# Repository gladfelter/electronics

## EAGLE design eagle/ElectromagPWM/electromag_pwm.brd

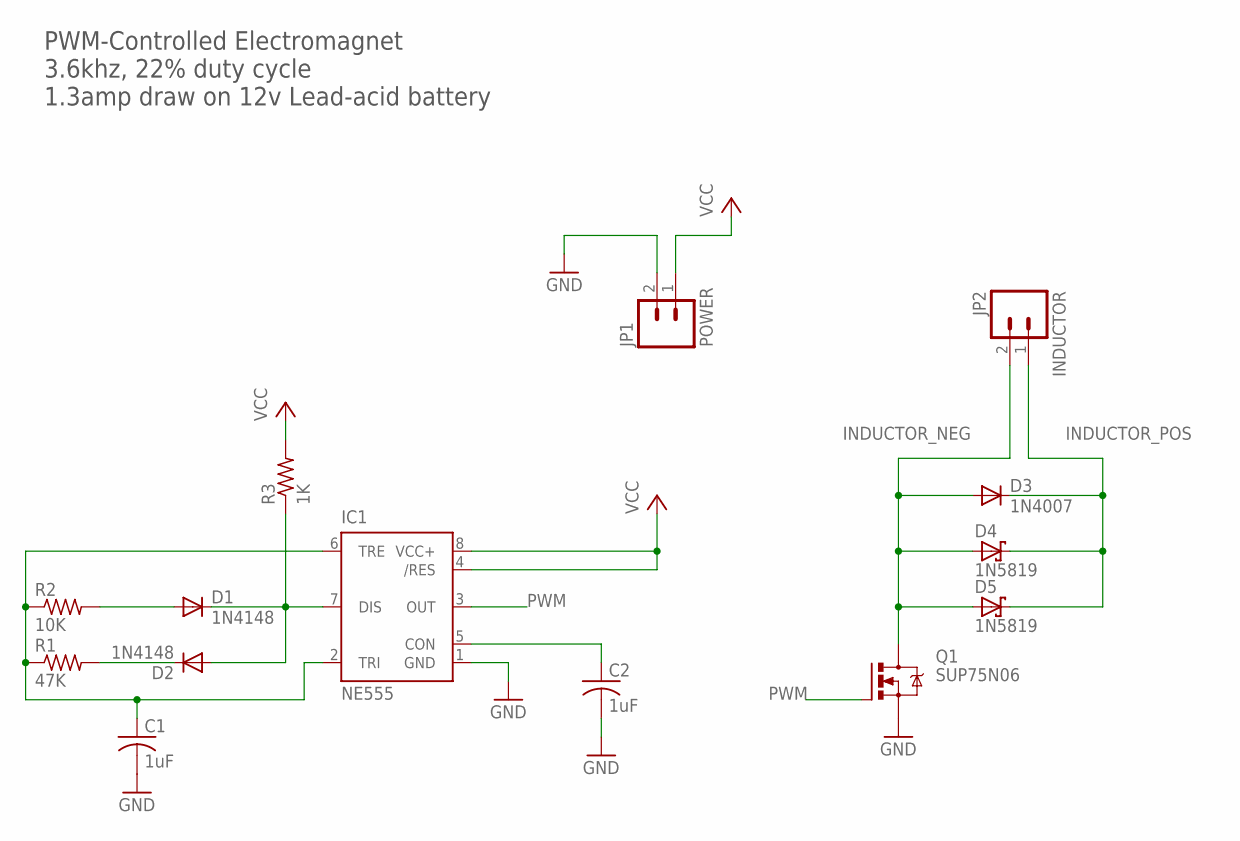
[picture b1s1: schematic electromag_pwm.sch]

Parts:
C1, C2: 1uF; C025-025X050
D1, D2: 1N4148; DO35-7
D3: 1N4007; DO41-10
D4, D5: 1N5819; DO41-7.6
IC1: NE555; DIL-08
JP1: POWER; JST-2-PTH-VERT
JP2: INDUCTOR; JST-2-PTH-VERT
Q1: SUP75N06; TO220BH
R1: 47K; 0204/5
R2: 10K; 0204/5
R3: 1K; 0204/5

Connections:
GND: C1.2, C2.2, IC1.1 (GND), JP1.2, Q1.S
INDUCTOR_NEG: D3.A, D4.A, D5.A, JP2.2, Q1.D
INDUCTOR_POS: D3.C, D4.C, D5.C, JP2.1
unnamed: D2.C, R1.2
unnamed: D1.A, R2.2
unnamed: C2.1, IC1.5 (CON)
unnamed: C1.1, IC1.2 (TRI), IC1.6 (TRE), R1.1, R2.1
unnamed: D1.C, D2.A, IC1.7 (DIS), R3.1
PWM: IC1.3 (OUT), Q1.G
VCC: IC1.4 (/RES), IC1.8 (VCC+), JP1.1, R3.2

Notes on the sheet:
PWM-Controlled Electromagnet 3.6khz, 22% duty cycle 1.3amp draw on 12v Lead-acid battery

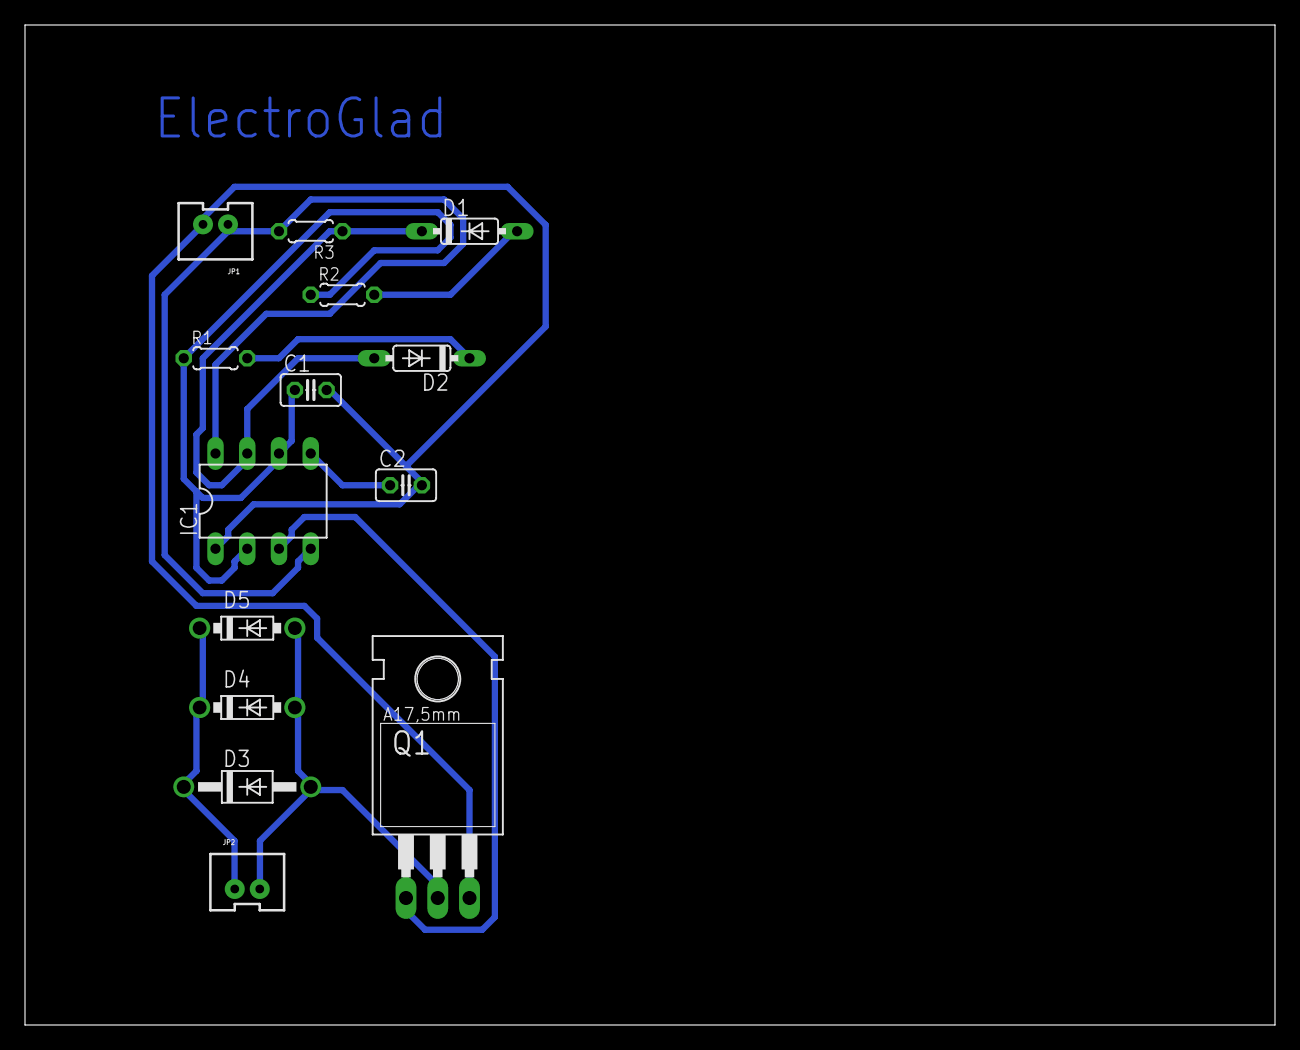
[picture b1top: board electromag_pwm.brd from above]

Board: 2 copper layers, 100.0 x 80.0 mm, 14 parts (0 on the bottom side), 10 nets.

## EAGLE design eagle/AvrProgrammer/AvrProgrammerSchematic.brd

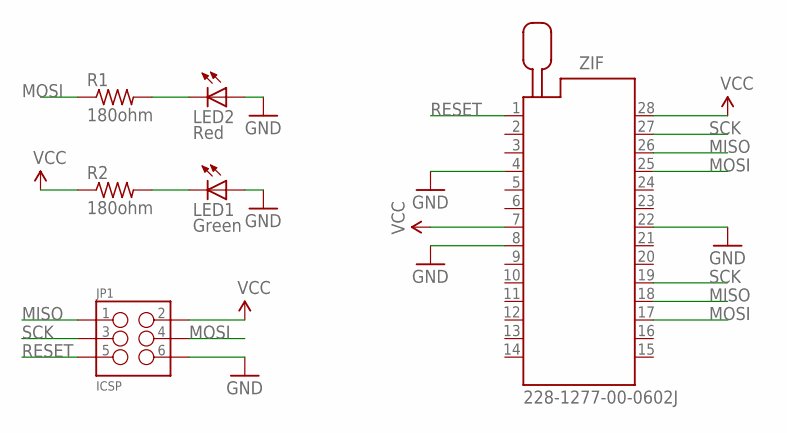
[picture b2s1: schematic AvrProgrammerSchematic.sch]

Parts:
JP1: ICSP; 2X3_SMD
LED1: Green; LED3MM
LED2: Red; LED3MM
R1, R2: 180ohm; 0207/7
ZIF: 228-1277-00-0602J

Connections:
GND: JP1.6, LED1.A, LED2.A, ZIF.4, ZIF.8, ZIF.22
MISO: JP1.1, ZIF.18, ZIF.26
MOSI: JP1.4, R1.1, ZIF.17, ZIF.25
unnamed: LED2.K (C), R1.2
unnamed: LED1.K (C), R2.2
RESET: JP1.5, ZIF.1
SCK: JP1.3, ZIF.19, ZIF.27
VCC: JP1.2, R2.1, ZIF.7, ZIF.28

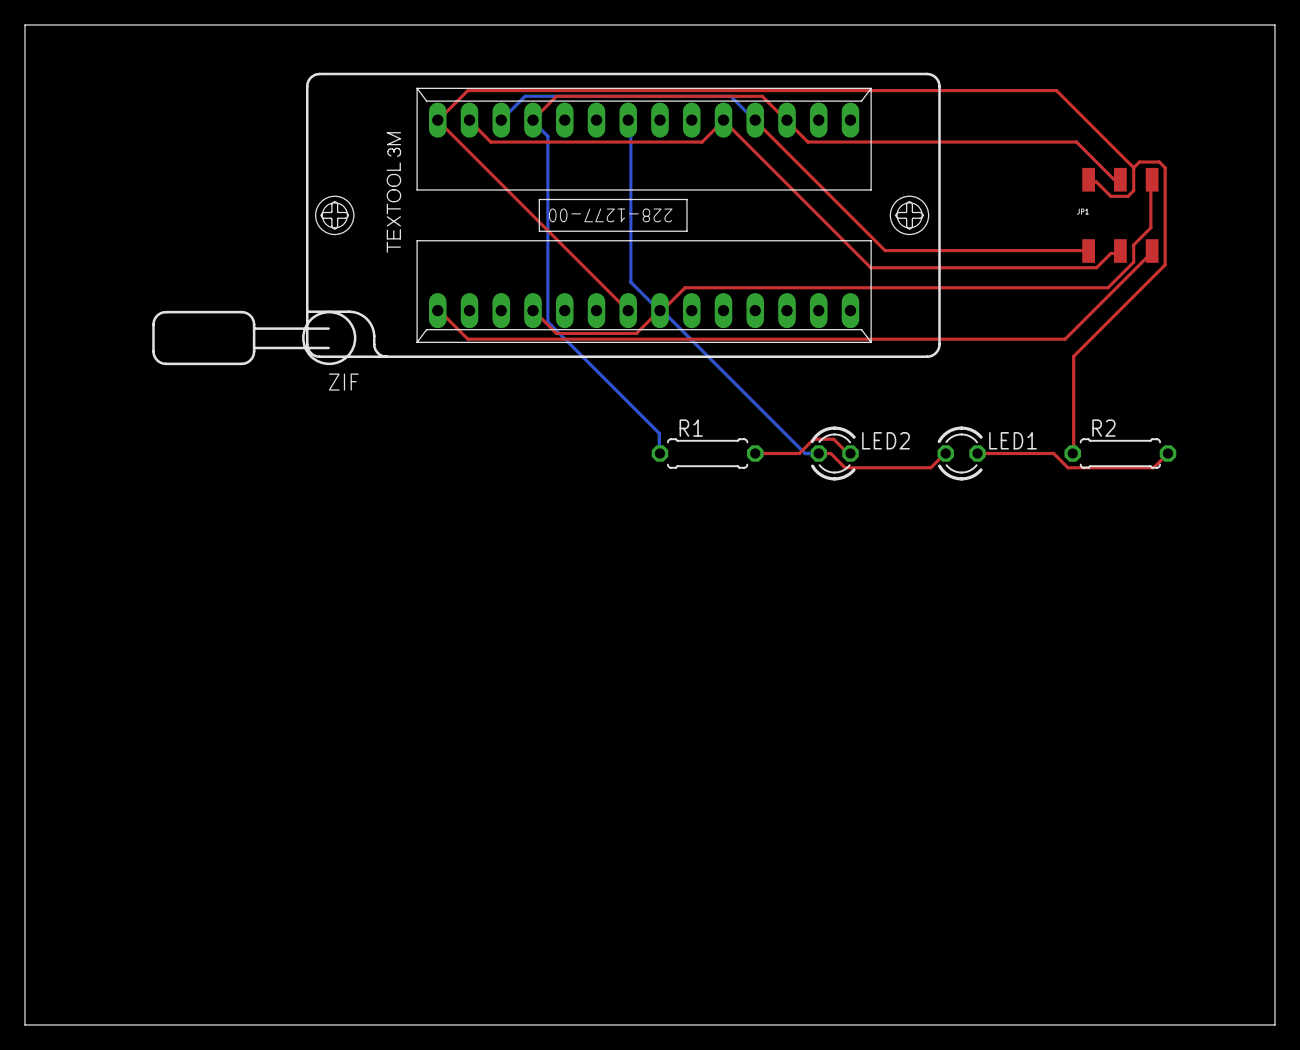
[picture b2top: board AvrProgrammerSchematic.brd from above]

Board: 2 copper layers, 100.0 x 80.0 mm, 6 parts (0 on the bottom side), 8 nets.

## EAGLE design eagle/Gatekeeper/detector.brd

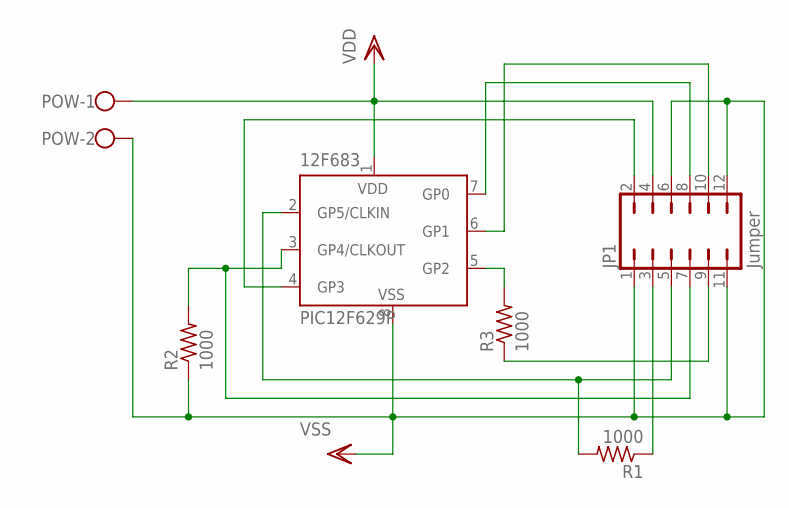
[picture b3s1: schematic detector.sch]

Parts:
12F683: PIC12F629P; DIL8
JP1: Jumper; JP6Q
POW: W237-102
R1, R2, R3: 1000; 0207/10

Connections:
unnamed: 12F683.2 (GP5/CLKIN), JP1.5, R1.2
unnamed: JP1.9, R3.1
unnamed: 12F683.3 (GP4/CLKOUT), JP1.7, R2.2
unnamed: JP1.3, R1.1
unnamed: 12F683.4 (GP3), JP1.2
unnamed: 12F683.6 (GP1), JP1.10
unnamed: 12F683.7 (GP0), JP1.8
unnamed: 12F683.5 (GP2), R3.2
VDD: 12F683.1 (VDD), JP1.4, POW.1
VSS: 12F683.8 (VSS), JP1.1, JP1.6, JP1.11, JP1.12, POW.2, R2.1

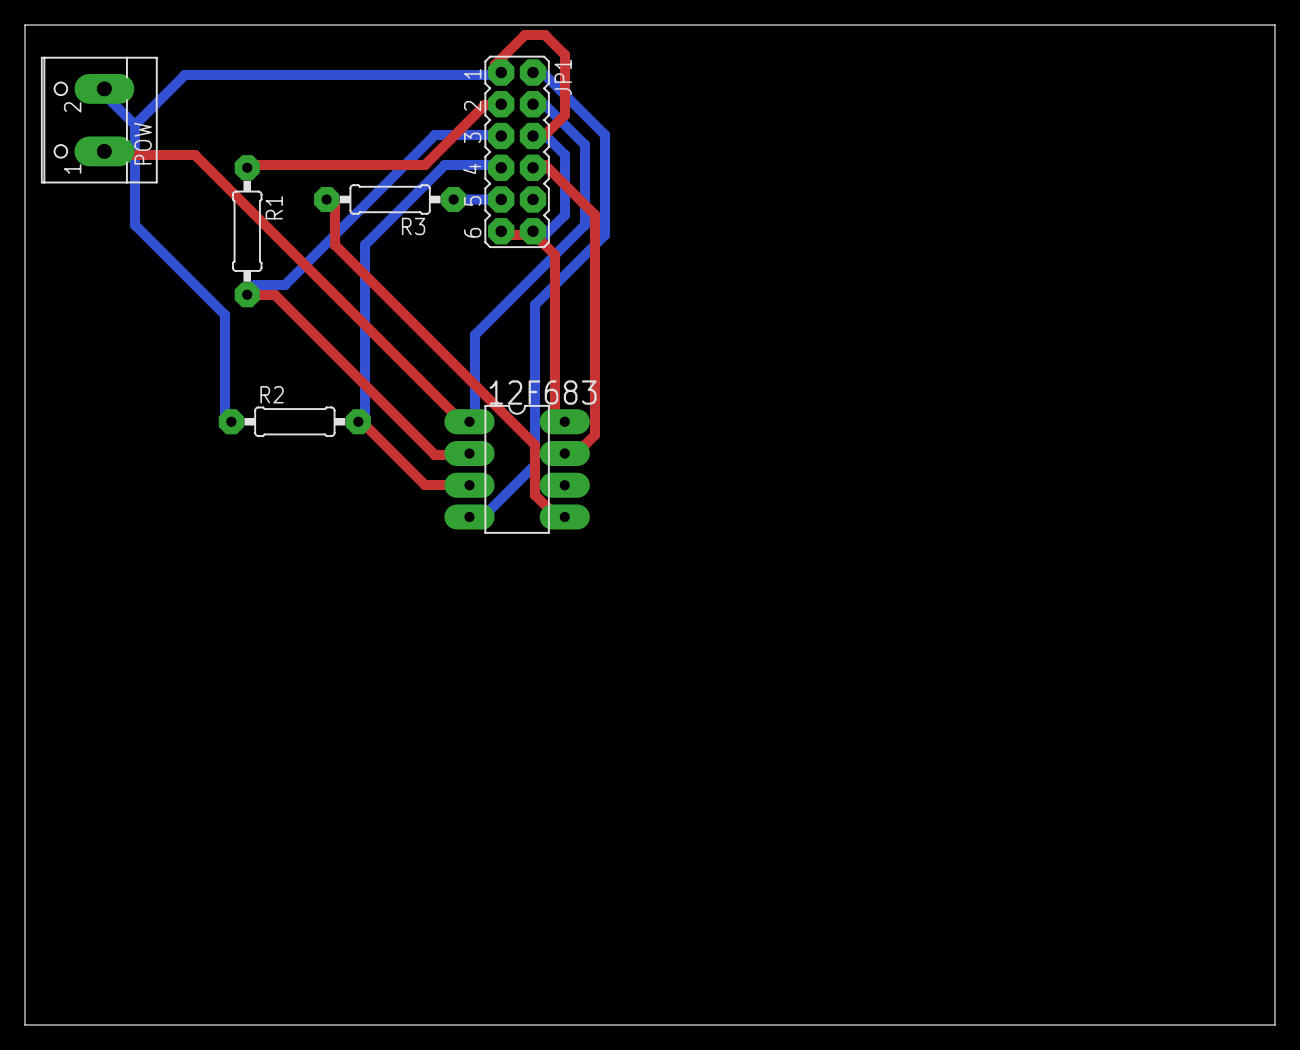
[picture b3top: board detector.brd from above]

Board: 2 copper layers, 100.0 x 80.0 mm, 6 parts (0 on the bottom side), 10 nets.

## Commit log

2014-08-10 adding gitignores
2014-08-10 initial checkin
2014-08-11 working on remote control project
2014-08-11 lcd working
2014-08-18 battery capacity project
2014-08-19 working on battery capacity project
2014-08-19 formatting
2014-08-24 still trying to get lcd to work on pic
2014-08-24 going to duplicate arduino lcd sequence
2014-08-24 lcd working!
2014-08-24 working, simplifying
2014-08-24 batcap project cleaned up and working
2014-08-25 cleaned up lcd library
2014-08-26 Mostly complete implementing a discharge cycle button. Next step is timing
2014-11-02 servo, driver for nano, battery capacity project
2015-01-03 adding a better tone pitch follower
2015-01-26 added logic 8, arduino onewire, oled libraries, created temp sensor with oled output sketch.
2015-07-02 recent projects
2015-07-12 recent work
2015-07-13 button array calibrated in eeprom. Works.
2015-07-15 ading button library to sd audio sketch
2015-07-15 sd button audio kind of working, needs another calibration, perhaps a more stable voltage source
2015-07-20 added eagle sketch, cleaned up sound box project
2015-07-21 working on a board for programming arduino
2015-09-14 adding non-standard eagle libraries, attiny13 arduino IDE support files, and sound box schematic. Also electromagnet project changes
2015-09-15 Created audio amplifier breakout library.
2015-09-15 finished sound box schematic
2016-06-14 board changes and neopixel

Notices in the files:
parts and their libraries:
SparkFun-Connectors: Licensing: Creative Commons ShareAlike 4.0 International - https://creativecommons.org/licenses/by-sa/4.0
